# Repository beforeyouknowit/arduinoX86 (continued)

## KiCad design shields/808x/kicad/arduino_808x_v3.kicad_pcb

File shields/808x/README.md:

## ArduinoX86 808X Shield

This shield supports the 8088, 8086, V20 and V30 CPUs.

It is designed for 3.3V operation.

If using an Arduino Due, you can power the CPU directly from the Arduino. This is the default mode of operation.
Despite being 5V parts, 3.3V operation appears to be fine for CMOS variants of the 8088/8086, the AMD D8088 and the V20
and V30 CPUs.

If using an Arduino GIGA, cut the 3.3V power pin from the headers as the Giga cannot supply enough power to run the CPU.
You can then choose to directly deliver either 3.3 or 5V of external power into the board's 3.3V power header.

> [!WARNING]  
> Do not feed power into the shield's power header unless you have cut the 3V header pin on the shield. Feeding power
> into
> the Arduino's 3V out pin will damage your Arduino.

Please read all the notes in the next section before ordering/assembling parts. Failure to heed warnings will cause
damage to your Arduino.

# BOM

- A compatible CPU. For best results, use a CMOS CPU such as a Harris 80C88, Oki 80C88, or NEC V20 CPU. Beware of
  counterfeits on eBay and other online vendors.
  A legitimate chip will not look shiny and new with perfect printing on it.

- (Optional) An Intel 8288 or OKI 82C88 Bus Controller. If not using an 8288, set the EMULATE_8288 flag in cpu_server.

- A set of Arduino stacking headers (also usable with DUE)
  https://www.amazon.com/Treedix-Stacking-Headers-Stackable-Compatible/dp/B08G4FGBPQ

- A DIP-40 and (optionally) DIP-20 socket
    - Optional: You can spring for a ZIF socket such
      as [https://www.amazon.com/-/en/gp/product/B00B886OZI](https://www.amazon.com/-/en/gp/product/B00B886OZI)

- (2x) 0805 0.047uf bypass capacitors
  https://www.mouser.com/ProductDetail/80-C0805C473KARAUTO

- (Optional) A 12mm, active buzzer with 7.6mm pin spacing.

    - For DUE: A 3V piezoelectric, low power buzzer <= 6mA
      https://www.mouser.com/ProductDetail/Mallory-Sonalert/PK-11N40PQ?qs=SXHtpsd1MbZ%252B7jeUyAAOVA%3D%3D

    - For MEGA: Any 3-5V buzzer <= 30mA
      WARNING: Only connect an electromagnetic buzzer if using an Arduino MEGA. The DUE has much lower GPIO max current
      supply.

- (2x) 750Ohm resistors (for LEDs)
  https://www.mouser.com/ProductDetail/667-ERA-6AED751V

- (2x) Any 0805 ~2V LED of your choice with 1.8-1.9mA forward current
    - https://www.mouser.com/ProductDetail/604-APTD2012LCGCK (Green)
    - https://www.mouser.com/ProductDetail/604-APT2012LSECKJ4RV (Orange)

- RS232 board for debug output - choose gender based on your desired cabling
    - https://www.amazon.com/Ultra-Compact-RS232-Converter-1Mbps/dp/B074BMLM11 (male)
    - https://www.amazon.com/Ultra-Compact-RS232-Converter-Female/dp/B074BTGLJN (female)
    - WARNING: DO NOT connect 5V to rs232 board on DUE

> [!TIP]
> The listed RS232 boards appear to be no longer available. You may try using any of the common MAX3232-based RS232
> breakout boards, but I've had mixed luck with them due to quality issues. The MAX3232 is also less capable so you may
> need to adjust the serial baud rate to be lower.

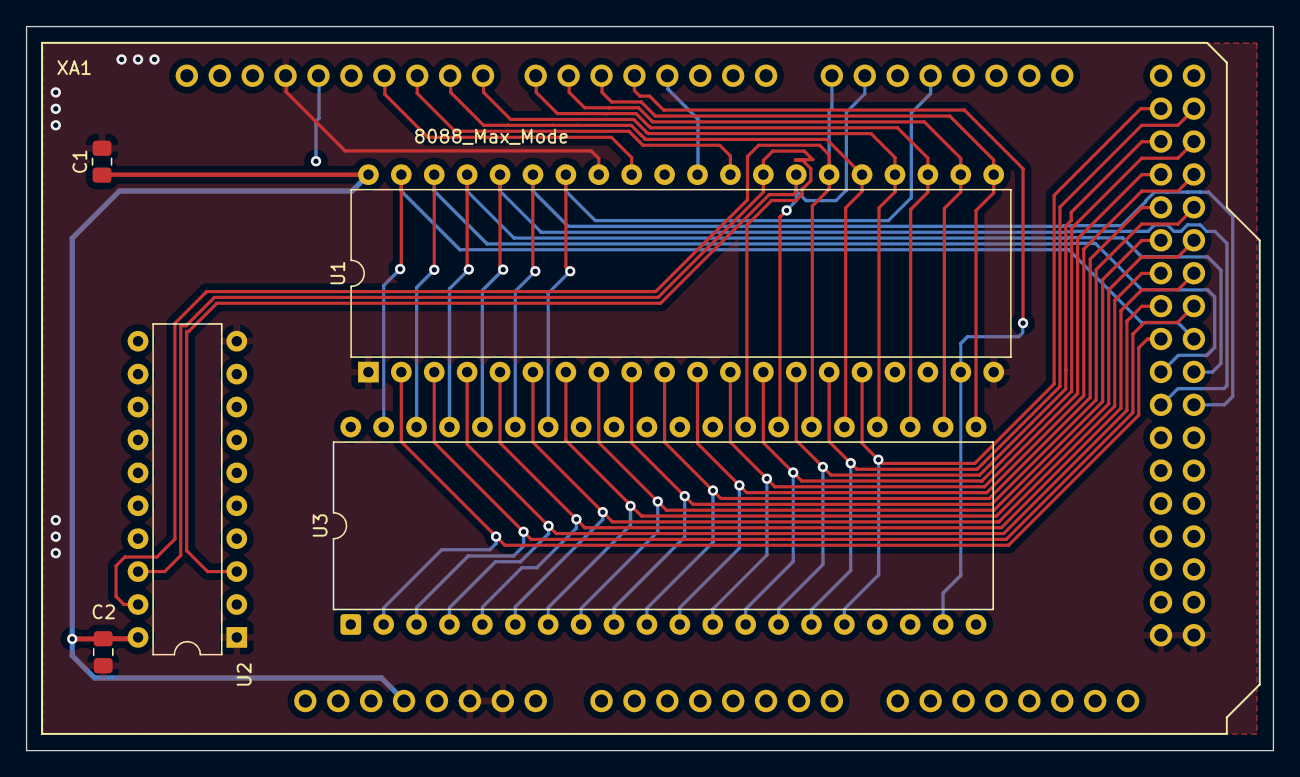
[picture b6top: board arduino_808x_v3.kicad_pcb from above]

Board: 2 copper layers, 96.2 x 55.9 mm, 6 parts (0 on the bottom side), 51 nets.

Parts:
C1, C2: 0.1uf; C_0805_2012Metric_Pad1.18x1.45mm_HandSolder
U1: 8088_Max_Mode; DIP-40_W15.24mm
U2: 8288; DIP-20_W7.62mm
U3: 8087; DIP-40_W15.24mm
XA1: Arduino_Mega2560_Shield

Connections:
+3.3V: C1.1, C2.1, U1.40 (VCC), U2.20 (VCC), U3.40 (VCC), XA1.3V3 (3.3V)
+5V: XA1.5V3 (5V), XA1.5V4 (5V)
/A8: U1.8 (A8), U3.8 (AD8), XA1.D30
/A9: U1.7 (A9), U3.7 (AD9), XA1.D31
/A10: U1.6 (A10), U3.6 (AD10), XA1.D32
/A11: U1.5 (A11), U3.5 (AD11), XA1.D33
/A12: U1.4 (A12), U3.4 (AD12), XA1.D34
/A13: U1.3 (A13), U3.3 (AD13), XA1.D35
/A14: U1.2 (A14), U3.2 (AD14), XA1.D36
/A15: U1.39 (A15), U3.39 (AD15), XA1.D37
/A16: U1.38 (A16/S3), U3.38 (A16/S3), XA1.D38
/A17: U1.37 (A17/S4), U3.37 (A17/S4), XA1.D39
/A18: U1.36 (A18/S5), U3.36 (A18/S5), XA1.D40
/A19: U1.35 (A19/S6), U3.35 (A19/S6), XA1.D41
/AD0: U1.16 (AD0), U3.16 (AD0), XA1.D22
/AD1: U1.15 (AD1), U3.15 (AD1), XA1.D23
/AD2: U1.14 (AD2), U3.14 (AD2), XA1.D24
/AD3: U1.13 (AD3), U3.13 (AD3), XA1.D25
/AD4: U1.12 (AD4), U3.12 (AD4), XA1.D26
/AD5: U1.11 (AD5), U3.11 (AD5), XA1.D27
/AD6: U1.10 (AD6), U3.10 (AD6), XA1.D28
/AD7: U1.9 (AD7), U3.9 (AD7), XA1.D29
/ALE: U2.5 (ALE), XA1.D50
/CEN: U2.15 (CEN), XA1.A1
/DEN: U2.16 (DEN), XA1.D44
/DT/~R: U2.4 (DT/~R), XA1.D49
/INTR: U1.18 (INTR), XA1.D12
/MCE/~PDEN: U2.17 (MCE/~PDEN), XA1.D43
/NMI: U1.17 (NMI), XA1.D13
/S0: U1.26 (~S0), U2.19 (~S0), U3.26 (~S0), XA1.D14 (D14_TX3)
/S1: U1.27 (~S1), U2.3 (~S1), U3.27 (~S1), XA1.D15 (D15_RX3)
/S2: U1.28 (~S2), U2.18 (~S2), U3.28 (~S2), XA1.D16 (D16_TX2)
/~AEN: U2.6 (~AEN), XA1.A0
/~AIOWC: U2.12 (~AIOWC), XA1.D48
/~AMWC: U2.8 (~AMWC), XA1.D52
/~INTA: U2.14 (~INTA), XA1.D45
/~IORC: U2.13 (~IORC), XA1.D46
/~IOWC: U2.11 (~IOWC), XA1.D47
/~LOCK: U1.29 (~LOCK), XA1.D10
/~MRDC: U2.7 (~MRDC), XA1.D51
/~MWTC: U2.9 (~MWTC), XA1.D53 (D53_SS)
/~RD: U1.32 (~RD), XA1.D11
/~RQ/~GT1: U1.30 (~RQ/~GT1), XA1.D3 (D3_INT1)
/~TEST: U1.23 (~TEST), U3.23 (BUSY), XA1.D7
CLK: U1.19 (CLK), U2.2 (CLK), U3.19 (CLK), XA1.D4
GND: C1.2, C2.2, U1.1 (GND), U1.20 (GND), U2.1 (IOB), U2.10 (GND), XA1.GND1 (GND), XA1.GND2 (GND), XA1.GND3 (GND), XA1.GND5 (GND), XA1.GND6 (GND)
QS0: U1.25 (QS0), U3.25 (QS0), XA1.D9
QS1: U1.24 (QS1), U3.24 (QS1), XA1.D8
READY: U1.22 (READY), U3.22 (READY), XA1.D6
RESET: U1.21 (RESET), U3.21 (RESET), XA1.D5
~BHE: U1.34 (HIGH), U3.34 (~BHE/S7), XA1.D17 (D17_RX2)

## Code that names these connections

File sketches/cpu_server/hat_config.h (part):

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#endif

// -------------------------- CPU Input pins ----------------------------------
#define BHE_PIN 17
#define READ_BHE_PIN READ_PIN_D17
#define READ_READY_PIN READ_PIN_D06
#define READ_TEST_PIN READ_PIN_D07
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
#define READY_PIN 6
#define TEST_PIN 7
#define LOCK_PIN 10
#define INTR_PIN 12
#define NMI_PIN 13

// -------------------------- CPU Output pins ---------------------------------
#define RQ_PIN 3

// --------------------------8288 Control Inputs ------------------------------
#define AEN_PIN 54
#define CEN_PIN 55

// --------------------------8288 Control lines -------------------------------
#define ALE_PIN 50
#define DTR_PIN 49
#define MCEPDEN_PIN 43
#define DEN_PIN 44

// --------------------------8288 Command lines -------------------------------
#define MRDC_PIN 51
#define AMWC_PIN 52
#define MWTC_PIN 53
#define IORC_PIN 46
#define AIOWC_PIN 48
#define IOWC_PIN 47
#define INTA_PIN 45

// -------------------------- Macro definitions  ---------------------------------

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#if EMULATE_8288
  // D50: PC13
  #if CPU_186
    // The 186 has its own ALE pin, so we will defer to that
    #define READ_ALE_PIN  READ_PIN_D50
  #else
    #define READ_ALE_PIN  (I8288.ale)
  #endif
  // D51: PC12
  #define READ_MRDC_PIN   (!I8288.mrdc)
  // D52: PB21
  #define READ_AMWC_PIN   (!I8288.amwc)
  // D53: PB14
  #define READ_MWTC_PIN   (!I8288.mwtc)
  // D46: PC17
  #define READ_IORC_PIN   (!I8288.iorc)
  // D48: PC15
  #define READ_AIOWC_PIN  (!I8288.aiowc)
  // D47: PC16
  #define READ_IOWC_PIN   (!I8288.iowc)
  // D45: PC18
  #define READ_INTA_PIN   (!I8288.inta)
#else
  #if defined(__SAM3X8E__) // If Arduino DUE
    
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      // decoded 
      #define READ_ALE_PIN      READ_PIN_D50
      #define READ_MRDC_PIN     !(!READ_PIN_D51 && READ_PIN_D16)    // We hook !RD up to D51. Mem read when S2 (D16) is high.
      #define READ_AMWC_PIN     1                                   // There is no AMWC signal. Simulate inactive-high.
      #define READ_MWTC_PIN     !(!READ_PIN_D53 && READ_PIN_D16)    // We hook !WR up to D53. Mem write when S2 (D16) is high.
      #define READ_IORC_PIN     !(!READ_PIN_D51 && !READ_PIN_D16)   // We hook !RD up to D51. IO read when S2 (D16) is low.
      #define READ_AIOWC_PIN    1                                   // There is no AIOWC signal. Simulate inactive-high.
      #define READ_IOWC_PIN     !(!READ_PIN_D53 && !READ_PIN_D16)   // We hook !WR up to D53. IO write when S2 (D16) is low.
      #define READ_INTA_PIN     READ_PIN_D45
    #else
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      // decoded 
      #define READ_ALE_PIN      READ_PIN_D50
      #define READ_MRDC_PIN     !(!READ_PIN_D51 && READ_PIN_D16)    // We hook !RD up to D51. Mem read when S2 (D16) is high.
      #define READ_AMWC_PIN     1                                   // There is no AMWC signal. Simulate inactive-high.
      #define READ_MWTC_PIN     !(!READ_PIN_D53 && READ_PIN_D16)    // We hook !WR up to D53. Mem write when S2 (D16) is high.
      #define READ_IORC_PIN     !(!READ_PIN_D51 && !READ_PIN_D16)   // We hook !RD up to D51. IO read when S2 (D16) is low.
      #define READ_AIOWC_PIN    1                                   // There is no AIOWC signal. Simulate inactive-high.
      #define READ_IOWC_PIN     !(!READ_PIN_D53 && !READ_PIN_D16)   // We hook !WR up to D53. IO write when S2 (D16) is low.
      #define READ_INTA_PIN     READ_PIN_D45
    #else
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
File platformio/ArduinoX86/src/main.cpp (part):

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  CPU.address_bus = Controller.readAddressBus(false);

  static CycleState cycle_state;
  bool ale = Controller.readALEPin();
  uint32_t server_flags = ArduinoX86::Server.get_flags();
  cycle_state.cpu_status0 = CPU.status0;
  cycle_state.bus_command_bits = CPU.command_bits;
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    cycle_state.pins = 0;

    if (ale) {
      cycle_state.pins |= CycleState::ALE;
    }
    if (Controller.readBHEPin()) {
      cycle_state.pins |= CycleState::BHE;
    }
    if (Controller.readLockPin()) {
      cycle_state.pins |= CycleState::LOCK;
    }
    if (Controller.readReadyPin()) {
      cycle_state.pins |= CycleState::READY;
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
      if (CPU.loadall_checkpoint == 0 && (CPU.address_latch() == SMM_LOAD_CHECKPOINT)) {
        Controller.getBoard().debugPrintf(DebugType::LOAD, false, "## LOAD_SMM_386: Passed checkpoint. Deasserting SMI. Next fetch should be for program\n\r");
        Controller.writePin(OutputPin::Smi, true); // SMI is active-low
        CPU.loadall_checkpoint = 1;
      }
    }
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
  if (CPU.bus_state == HALT) {
    Controller.getBoard().debugPrintln(DebugType::EXECUTE, "## EXECUTE: HALT detected - Ending program execution.");
    Controller.writePin(OutputPin::Nmi, true);

    if (CPU.cpu_type != CpuType::i80386) {
      // The 386 keeps a persistent HALT bus state, so we can't return or we'll never escape it.
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    // Use checkpoint "1" to specify that NMI has been detected. This just prevents the debug message from
    // printing every cycle after NMI.
    if (CPU.nmi_checkpoint == 0) {
      Controller.getBoard().debugPrintln(DebugType::EXECUTE, "## EXECUTE: NMI pin high - Execute will end at IVT fetch.");
      CPU.nmi_checkpoint = 1;
    }
  }
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  if (!READ_SMI_PIN) {
    Controller.getBoard().debugPrintln(DebugType::EXECUTE, "## EXECUTE: SMI asserted.");
    // Sometimes the bus is PASV[1] on 386 during ADS. Not sure why.
    Controller.getBoard().debugPrintf(DebugType::EXECUTE, false, "## EXECUTE: SMI asserted, ads is %s, bus state is %d\n\r", Controller.readALEPin() ? "high" : "low", (CPU.status0 & 0xF));
    if (Controller.readALEPin() && ((CPU.bus_state == MEMW) || ((CPU.status0 & 0xF) == 1))) {

      Controller.getBoard().debugPrintln(DebugType::EXECUTE, "## EXECUTE: ALE high and MEMW cycle detected.");
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  if ((READ_NMI_PIN) && (CPU.nmi_checkpoint == 0)) {
    // Use checkpoint "1" to specify that NMI has been detected. This just prevents the debug message from
    // printing every cycle after NMI.
    Controller.getBoard().debugPrintln(DebugType::EXECUTE, "## EXECUTE: NMI pin high - Execute will end at IVT fetch.", true);
    CPU.nmi_checkpoint = 1;
    ArduinoX86::CycleLogger->disable_logging();
  }
  else if ((!READ_SMI_PIN) && (CPU.smi_checkpoint == 0)) {
    Controller.getBoard().debugPrintln(DebugType::ERROR, "## EXECUTE: SMI pin asserted - Execute will end at SMRAM write.", true);
    CPU.smi_checkpoint = 1;
    ArduinoX86::CycleLogger->disable_logging();
  }
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      if (CPU.use_smm()) {
        Controller.getBoard().debugPrintln(DebugType::EXECUTE, "## EXECUTE: HALT with SMM enabled.");
        if (READ_SMI_PIN) {
          Controller.getBoard().debugPrintln(DebugType::EXECUTE, "## EXECUTE: HALT - Writing SMI pin low", true);
          //Controller.writePin(OutputPin::Ready, true);
          Controller.writePin(OutputPin::Smi, false);
        }
      }
      else {
        Controller.getBoard().debugPrintln(DebugType::EXECUTE, "## EXECUTE: HALT with SMM disabled.");
        if (!READ_NMI_PIN){
          Controller.getBoard().debugPrintln(DebugType::EXECUTE, "## EXECUTE: HALT - Writing NMI pin high.", true);
          Controller.writePin(OutputPin::Nmi, true);
        }
      }
    }
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        Controller.writeDataBus(CPU.data_bus, CPU.data_width);

        if (CPU.nmi_checkpoint == 1 && CPU.address_latch() == 0x0000A) {
          Controller.getBoard().debugPrintln(DebugType::EXECUTE, "## EXECUTE_FINALIZE: Read of NMI IVT with NMI pin high - Resetting STORE PC");
          CPU.nmi_checkpoint = 2;
          CPU.data_bus_resolved = true;
          CPU.s_pc = 0;
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
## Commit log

2025-06-19 migrate to platformio
2025-07-03 initial 80286 support
2025-07-06 286 remote execution working
2025-07-08 286 test generator
2025-07-12 more work on 286 test generator, MOO crate
2025-07-14 nearly final 286 test generator. initial test set generation
2025-07-19 move MOO crate to own repo
2025-07-21 final 286 generation state
2025-07-27 386 code execution and register readout
2025-07-27 Add KiCad projects for 286 and 386 HATs
2025-08-01 client: Fix 386 descriptor order, add RegisterPrinter
2025-08-01 add arduinox86_egui
2025-08-01 add automatic mode
2025-08-01 first steps toward 386 test generation
2025-08-01 add JTAG header, connect SMI pins
2025-08-01 update gitignore for kicad lck files
2025-08-02 arduinox86 GUI
2025-08-10 add 386EX+387SX hat
2025-08-10 more 386 support
2025-08-16 support for GetServerState, more 386 generation support
2025-08-16 support for GetServerState, CmdServerStatus, 386 exception detection
2025-08-16 update configs for 386 gen
2025-08-16 update gitignore
2025-08-16 arduinox86_gui: add scheduler, polling ServerStatus
2025-08-16 build asm
2025-08-16 fix conditional moo inclusion
2025-08-17 commit 386ex setup program source
2025-08-17 remove spurious 00 byte from 386ex setup
2025-08-17 vastly increase cpu setup cycle timeout
2025-08-24 comments
2025-08-24 register load in SMM, single-stepping in gui, register readout in gui
2025-08-24 rename hats->shields
2025-08-24 remove backup zips
2025-08-24 experimental 486 shield layout
2025-08-24 add FLAG_LOG_CYCLES
2025-08-24 avoid divide by 0 when cycle logging is disabled
2025-08-24 more speed optimizations
2025-08-31 fixes for 387, binary size control, memory update rate control
2025-08-31 commit some example programs
2025-09-01 fix SMIACT pin
2025-09-01 improve cycle state display in client lib and gui
2025-09-04 silence unqualified debug
2025-09-04 improve SMM handling
2025-09-04 change default descriptor for CS to data segment
2025-09-04 improve register load, add dtr option to serial connet
2025-09-04 add 'resolve bus when stepping' option
2025-09-04 add 'rom' binary type, normalize regs on load
2025-09-04 more 386ex support - utilize SMM for subsequent register loading
2025-09-06 more test generator improvements for 386
2025-09-07 add halt after jump ServerFlag
2025-09-07 add Opcode type
2025-09-07 fix ESP masking
2025-09-11 Fixes for mac
2025-09-11 add 386 32-bit address calculation to test generator
2025-09-11 update shields
2025-09-11 reorganize asm files
2025-09-11 add CmdSetProgramBounds
2025-10-14 Added macOS .DS_Store to .gitignore.
2025-10-14 386EX_V4 updated to V5 with 4-layer PCB.
2025-10-14 386EX_V4 PCB render updated; added preliminary HTML BOM.
2025-10-14 Added I2C SDA, SCK, ~ERROR and ~LOCK pull-up resistors; resolved minor DRC errors.
2025-10-14 Fixed bug from previous commit, R13 was wired to ~LOCK, was supposed to be to ~BUSY, corrected in this commit.
2025-10-14 Fixed oversight of I2C SDA and SCK pull-up resistors; rearranged EEPROM IC to accommodate.
2025-10-19 Added 2x 1N4148 diodes for combining 3.3V off-board supplies, updated HTML BOM.
2025-10-20 Updated 386EX to rev 5.1; added LDL1117 LDO, swapped to SMD diodes, tidied schematic.
2025-12-11 v5.1 commit with various improvements, updated README.
2025-12-11 Reverted 386EX_V4 to track with original fork of repo.
2026-03-07 bugfix for HashBackend
2026-03-07 bugfix for SMM load, add set_jump_hint command
2026-03-07 Fixes for HashBackend, support for set_memory
2026-03-07 add support for HashBackend to cmd_read_memory
2026-03-07 improve exception and flag handling, add global tracing
2026-03-07 386EX: enable LOCK pin
2026-03-07 various improvements for 386 test generation.
2026-03-07 commit old changes for 386 test gen
2026-03-07 disable noisy debug
2026-03-07 remove extraneous newline
2026-03-07 push up whatever the heck i was working on a year ago
2026-03-07 disable extended IO in 386EX setup routine
2026-03-07 move profile section to workspace
2026-03-07 impl From<&RemoteCpuRegistersV3B> for RemoteCpuRegistersV3A
2026-03-07 cargo update
2026-03-07 fix NASM_PATH resolution
2026-03-07 Revert added files in shields/386ex_v4/
2026-03-07 try again to revert the V4 dir
2026-03-07 oh, to have my v4 back again
